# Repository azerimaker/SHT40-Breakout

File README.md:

# SHT4x Breakout
Sensirion [SHT4x](https://www.sensirion.com/en/environmental-sensors/humidity-sensors/humidity-sensor-sht4x/) Breakout board with Qwiic/STEMMA QT connectors and breadboard friendly pin headers.

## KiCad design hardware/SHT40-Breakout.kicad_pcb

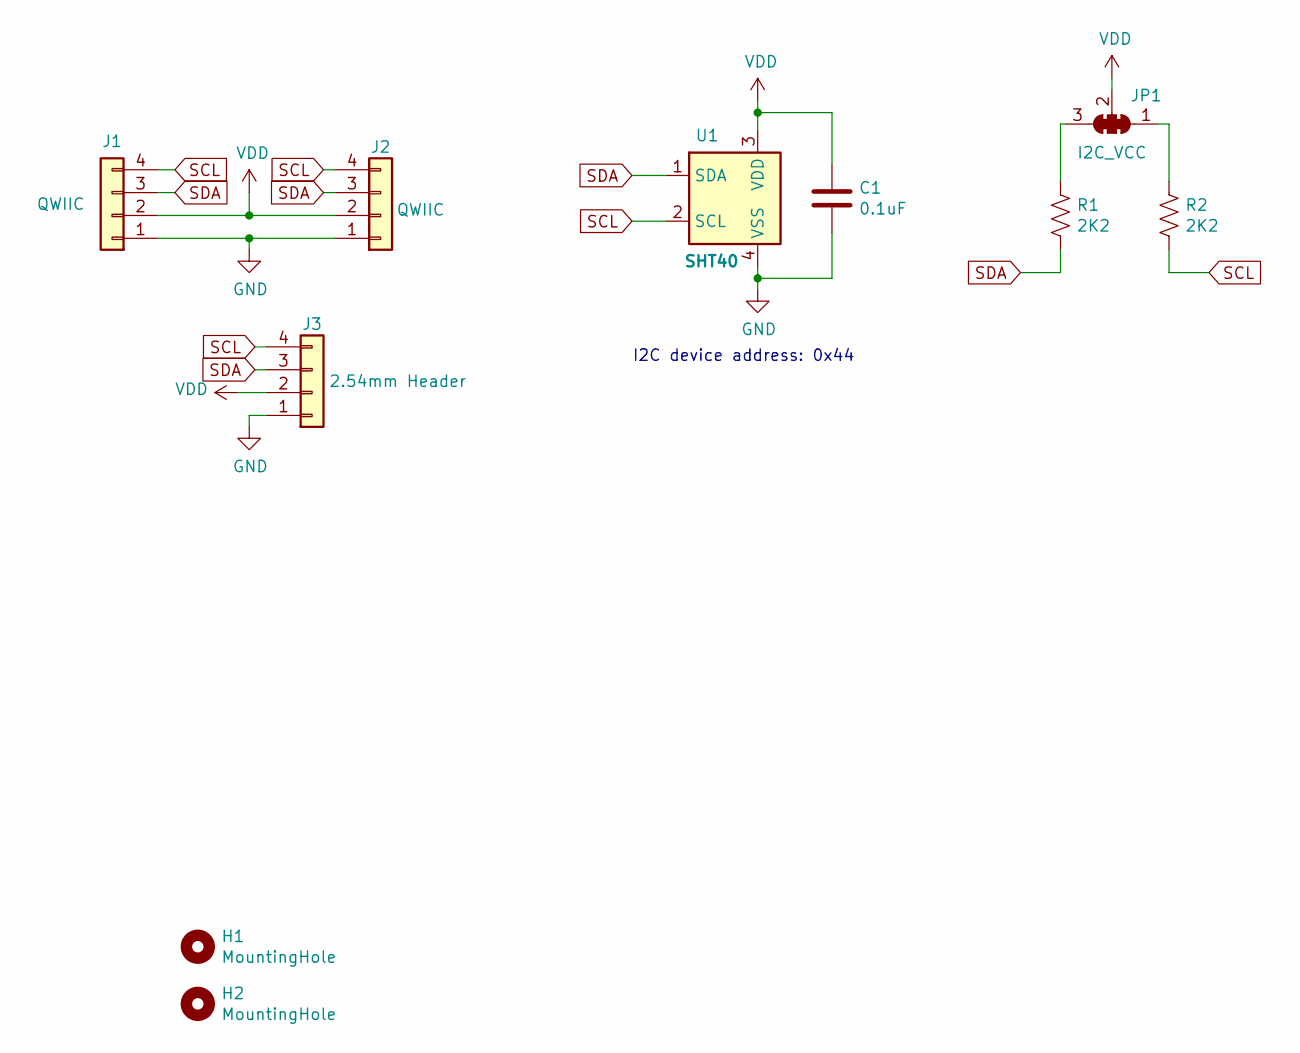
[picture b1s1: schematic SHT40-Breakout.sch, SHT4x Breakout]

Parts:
C1: 0.1uF; C_0603_1608Metric
H1, H2: MountingHole; MountingHole_2.7mm_M2.5_DIN965_Pad
J1, J2: QWIIC; JST_SH_SM04B-SRSS-TB_1x04-1MP_P1.00mm_Horizontal
J3: 2.54mm Header; PinHeader_1x04_P2.54mm_Vertical
JP1: I2C_VCC; SolderJumper-3_P1.3mm_Open_RoundedPad1.0x1.5mm
R1, R2: 2K2; R_0402_1005Metric_Pad0.72x0.64mm_HandSolder
U1: SHT40; DFN-4_1x1mm_P0.65mm

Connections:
GND: C1.2, J1.1, J2.1, J3.1, U1.4 (VSS)
unnamed: JP1.1 (A), R2.1
unnamed: JP1.3 (B), R1.1
SCL: J1.4, J2.4, J3.4, R2.2, U1.2 (SCL)
SDA: J1.3, J2.3, J3.3, R1.2, U1.1 (SDA)
VDD: C1.1, J1.2, J2.2, J3.2, JP1.2 (C), U1.3 (VDD)

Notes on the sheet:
I2C device address: 0x44

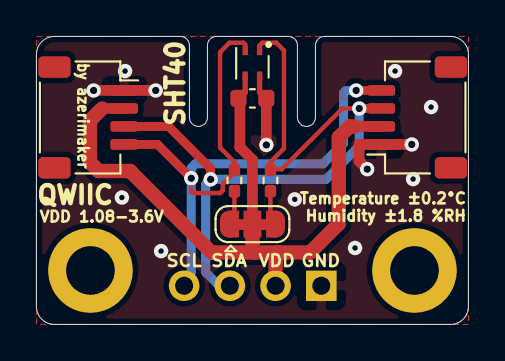
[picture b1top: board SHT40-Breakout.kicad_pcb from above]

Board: 2 copper layers, 24.0 x 16.0 mm, 10 parts (1 on the bottom side), 6 nets.

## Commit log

2021-04-19 doc, sch, pcb: Adding all the design files
2021-04-19 doc: Readme update
